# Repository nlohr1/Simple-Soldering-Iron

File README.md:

# Simple-Soldering-Iron
Simple Soldering-Iron - reverse-engeneered and modified to a half-phase-"dimmer", adding a diode for 230VAC.

Many Cheap Soldering-Irons came with simple Phase control steering, similar to dimmer-controls for lamps.  
Originally dimensioned for 115VAC, they are overheating at 230VAC, burning through in short time, because  
the Wattage becomes four times greater as intended.  
If you purchased one of these, its no need to give up - simply convert the circuit from full phase-control  
to a half phase-control, insering a small generic Diode between the RC-link and the Diac, so this Diode  
lets pass only one phase of the main-voltage. Therefore the generated power results normal (about 60W) and  
temperatures of the iron don't run-away.

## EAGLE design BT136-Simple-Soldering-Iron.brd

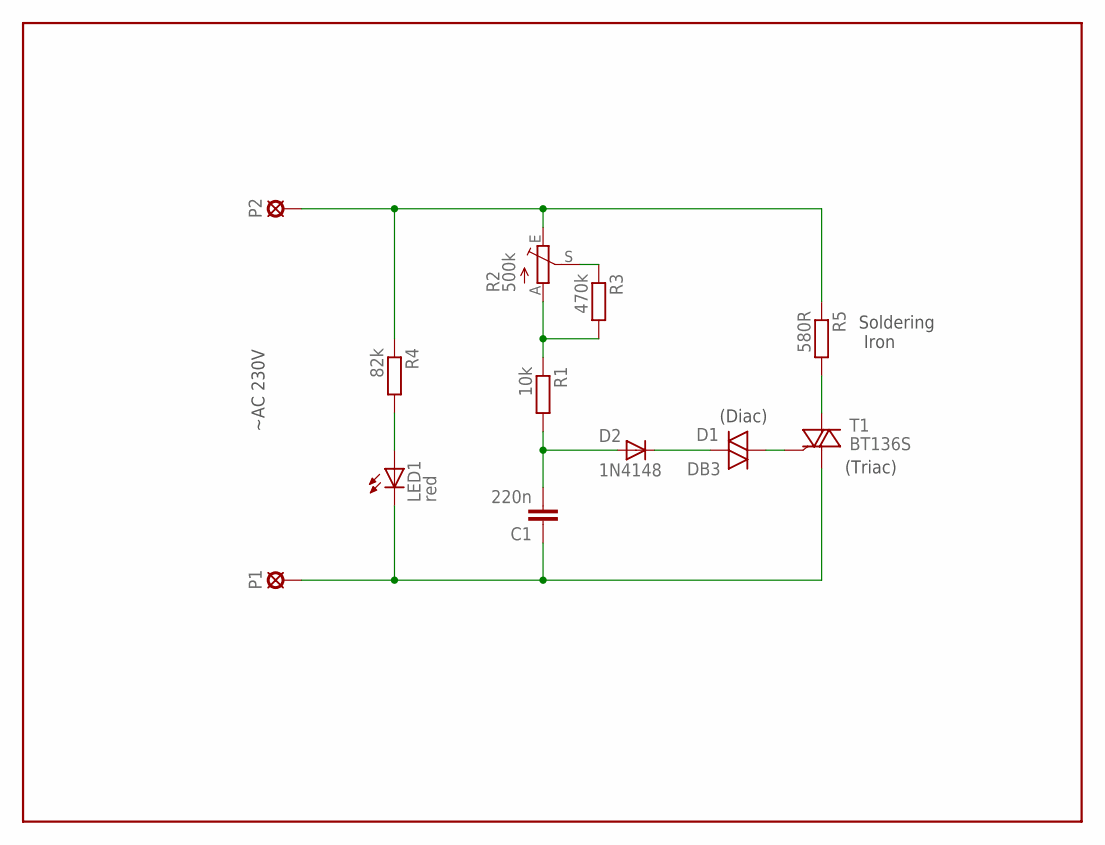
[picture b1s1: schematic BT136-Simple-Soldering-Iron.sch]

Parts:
C1: 220n; C050-025X075
D1: DB3; ER900
D2: 1N4148; DO35-7
LED1: red; SML1206
P1, P2: LSP10
R1: 10k; R1210
R2: 500k; RS3
R3: 470k; R1210
R4: 82k; R1210
R5: 580R; 0207/7
T1: BT136S; DPAK

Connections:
unnamed: D1.1, T1.3 (G)
unnamed: C1.2, D2.A, R1.2
unnamed: C1.1, LED1.C, P1.MP, T1.1 (A1)
unnamed: R1.1, R2.A, R3.2
unnamed: R2.S, R3.1
unnamed: R5.2, T1.4 (A2)
unnamed: P2.MP, R2.E, R4.1, R5.1
unnamed: D1.2, D2.C
unnamed: LED1.A, R4.2

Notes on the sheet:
Soldering Iron
~AC 230V
(Diac)
(Triac)

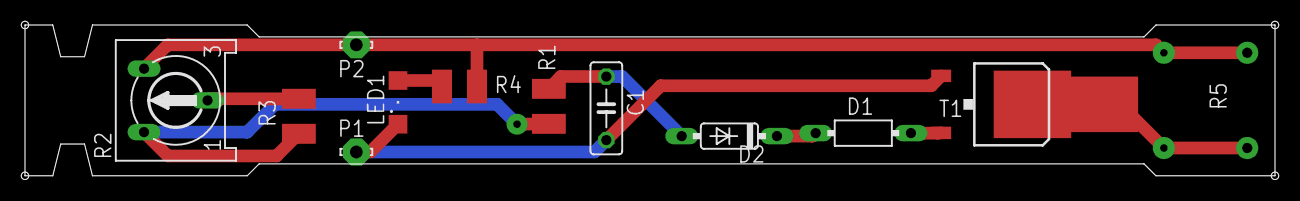
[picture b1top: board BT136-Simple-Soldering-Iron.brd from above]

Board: 2 copper layers, 100.0 x 12.1 mm, 12 parts (1 on the bottom side), 9 nets.
